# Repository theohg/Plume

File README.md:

<p align="center" width="100%">
  <picture>
    <source media="(prefers-color-scheme: dark)" srcset="./Logos/Plume_logo_light.png">
    <source media="(prefers-color-scheme: light)" srcset="./Logos/Plume_logo_dark.png">
    
  </picture>
</p>

Plume was designed by Théo Heng for the Integrated Actuators Laboratory [(LAI)](https://www.epfl.ch/labs/lai/) in the context of a master semester project. The goal is to develop a microcontroller-based system to independently control a motor array in a reconfigurable insole designed for patients with diabetes, redistributing plantar pressure without the use of position sensors. 

This board is capable to drive and control in position up to 18 Brushed DC motors total and up to 9 simultaneously, without position sensors. This is achieved thanks to the ripple counting technique, integrated in the DRV8214 drivers. 

Plume also integrates multiple other features: 
- Automotive Grade Wireless Charging Qi (WPC v2.0) 
- USB-C charging
- Power Path between USB and Induction
- BLE 5.4
- Adressable RGB LED
- Power LED, Charge LED, Fault LEDs
- Exposed UART and I2C interface
- Tag-Connect 2030 for SWD + SWO
- Battery Protection and Voltage Supervisor
- 6-axis, High Performance, low power IMU
- Motion-Controlled Deep-Sleep mode
- I2C Multiplexer
- Accurate and Low-Power Battery Voltage Sensing

***

***

## SPECIFICATIONS

| Parameter | Plume V1.0 | 
| --- | --- |
| Working Battery Voltage Input | 3.08-4.25 V |
| Typ. Charge Current (USB, wireless)| 455 mA |
| Max. Allowed Charge Current | 2.27 A |
| Max. Continuous Discharge Current | 4.54 A |
| Theoretical Deep Sleep Power Consumption| 15 µA |
| Mass | 23.5g with the frame |
| Communication | UART / Trace Asynchronous (SWD) / I2C |
| MCU | STM32 WB5MMGH6TR |
| Dimensions | 70x40x9mm |
| Cost per PCB    | 39 CHF board + 75 CHF components + 125 CHF assembly ≈ 240 CHF / PCB    |
| Designer   | Théo Heng        |
| Supervisors   | Maël Dagon, Paolo Germano      |
| Development Period       | Feb. - May. 2025 |
| Project    | Smart Footwear for Diabetic Foot Care    |

***

## DIRECTORY STRUCTURE

```
Plume
├── Computations        # Computation sheets and simulations performed
├── Datasheets          # Datasheet of components
├── Images              # Pictures and screenshots used in schematics
├── lib
    |── 3d_models       # Component 3D models
    |── lib_fp          # Footprint libraries
    └── lib_sym         # Symbol libraries
├── Logos               # EPFL and Plume logos
├── Manufacturing
    |── Assembly        # BOM, assembly document
        |── bom.csv     # CSV BOM
        |── bom.html    # HTML BOM
        └── ibom        # HTML interactive BOM
    └── Fabrication     # zipped fabrication documents, and other generated documents by JLCToolkit Pluggin
├── Schematic           # PDF of schematic
├── Software            # Firmware of the Board
    |── PLUME_ESP32     # PlatformIO project for the ESP32-based prototype
    └── PLUME_STM32     # STM32CubeIDE project for the Plume PCB
├── STEP_BLENDER_STL    # Step, .pcb3d and stl files of the PCB and its casing
└── Templates           # Title block templates

```

***

## FIRMWARE

***

## CREDITS

Schematic template & project structure is hugely inspired by the work of Vincent Nguyen on its [Λ M U L E T](https://github.com/EPFLXplore/XRE_LeggedRobot_HW/tree/master/amulet_controller) controler.

***

## PHOTOS

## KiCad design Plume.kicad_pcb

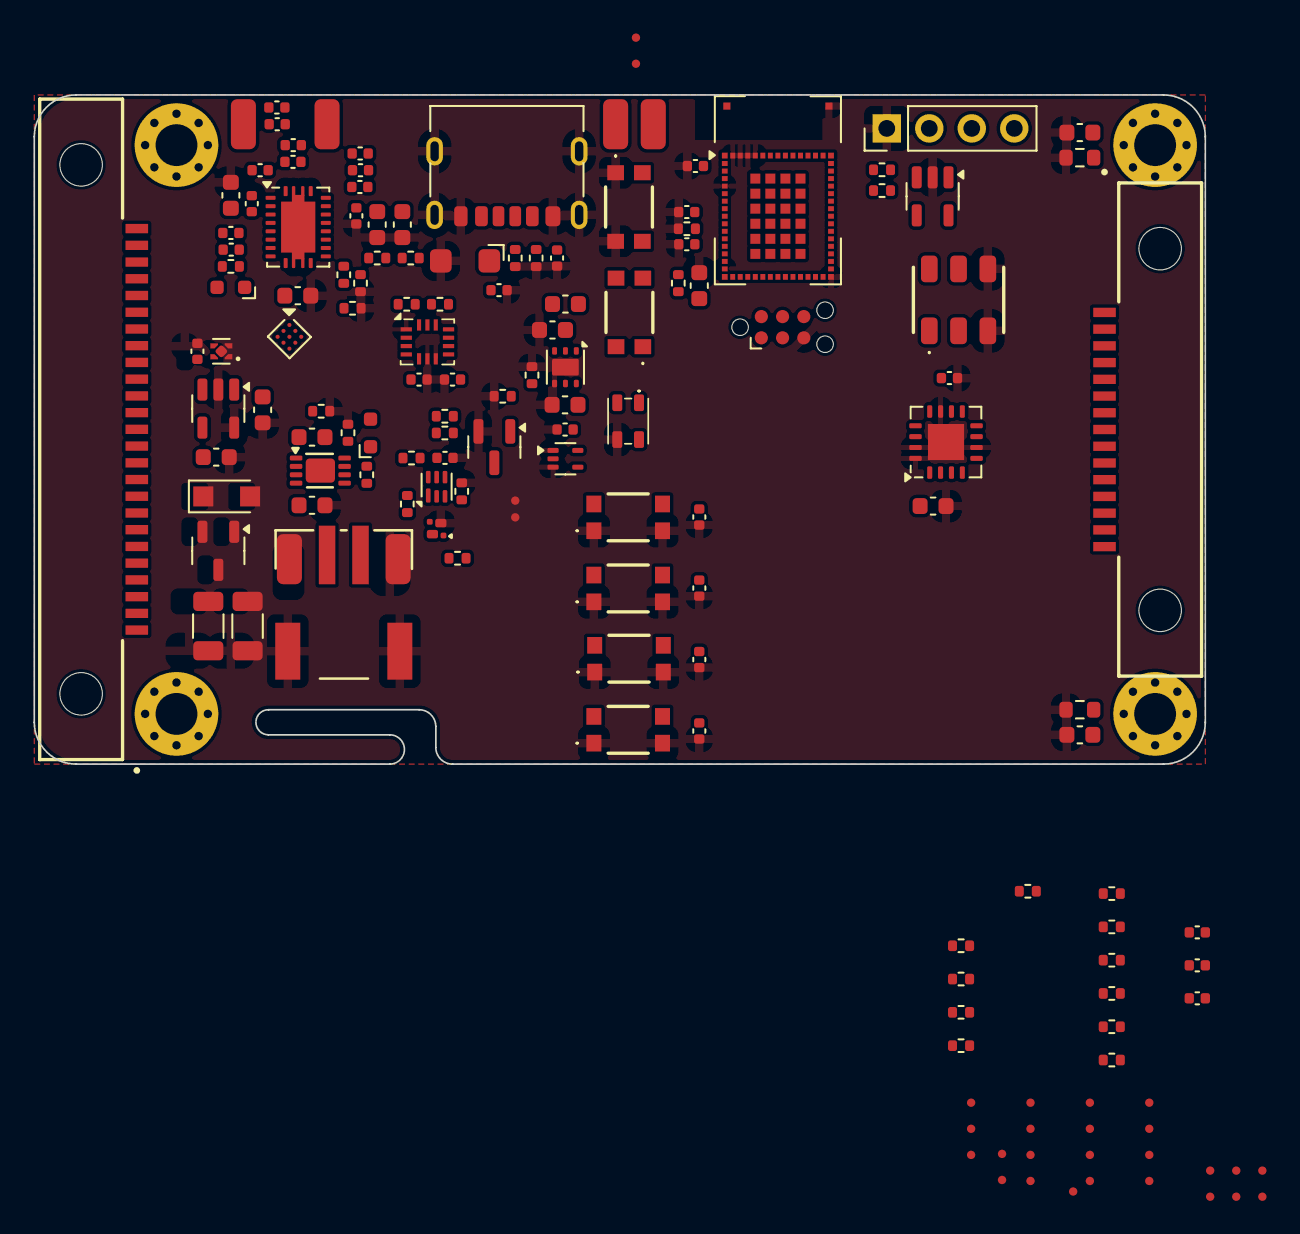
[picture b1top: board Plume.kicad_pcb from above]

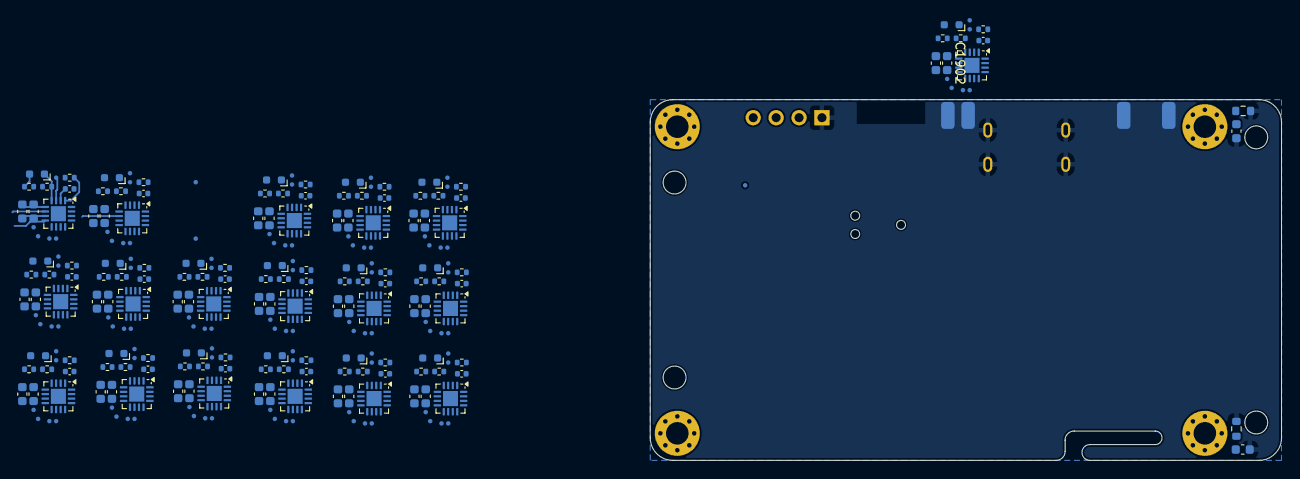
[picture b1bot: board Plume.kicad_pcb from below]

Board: 6 copper layers, 70.0 x 40.0 mm, 418 parts (262 on the bottom side), 203 nets.

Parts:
C401, C402, C404, C405, C406, C407, C502, C503, C601, C604, C605, C616, C701, C802, C1003, C1103, C1203, C1303, C1403, C1503, C1603, C1703, C1803, C1903, C2003, C2103, C2203, C2303, C2403, C2503, C2603, C2703, C2803, C2805, C2806: 100n X7R 16V; C_0402_1005Metric
C403, C501, C504: 4u7 X7R 16V; C_0603_1608Metric
C408, C409, C410: 3p3 C0G 50V; C_0402_1005Metric
C506, C507: 47u X5R 16V; C_1206_3216Metric
C602, C617, C618, C703, C704, C1001, C1101, C1201, C1301, C1401, C1501, C1601, C1701, C1801, C1901, C2001, C2101, C2201, C2301, C2401, C2501, C2601, C2701: 10u X5R 16V; C_0603_1608Metric
C603, C801: 1u X7R 16V; C_0603_1608Metric
C606, C609, C615: 10n C0G 25V; C_0402_1005Metric
C607, C613: 470n X5R 25V; C_0402_1005Metric
C608, C614: 22n X7R 25V; C_0402_1005Metric
C610: 150n X7R 25V; C_0402_1005Metric
C611: 2n2 X7R 25V; C_0402_1005Metric
C612: 390pF X7R 25V; C_0402_1005Metric
C1002, C1102, C1202, C1302, C1402, C1502, C1602, C1702, C1802, C1902, C2002, C2102, C2202, C2302, C2402, C2502, C2602, C2702: 100n X7R 50V; C_0603_1608Metric
C2801: 220n X7R 16V; C_0603_1608Metric
C2802, C2804: 2u2 X7R 16V; C_0603_1608Metric
C2901, C2902, C2903, C2904: 1n X7R 1kV; C_0603_1608Metric
D401: ESDS314; SOT-23-5
D601: TVS SMF5.0A; D_SOD-123FL
D701: Schottky 1N5819W; Nexperia_CFP3_SOD-123W
D2801: IN-PI22TAT5R5G5B; INPI22TAT5R5G5B
H2901, H2902, H2903, H2904: M2.5 (2.7mm); MountingHole_2.5mm_Pad_Via
IC1001, IC1101, IC1201, IC1301, IC1401, IC1501, IC1601, IC1701, IC1801, IC1901, IC2001, IC2101, IC2201, IC2301, IC2401, IC2501, IC2601, IC2701: DRV8214RTER; WQFN-16-1EP_3x3mm_P0.5mm_EP1.68x1.68mm_ThermalVias
IC2801: SN74AHCT1G125DRLR; SOT-553
IC2802: REG71050DRVT; WSON-6-1EP_2x2mm_P0.65mm_EP1x1.6mm
J401: Solder Holes 4x1 2.54mm 22AWG; PinHeader_1x04_P2.54mm_Vertical
J402: Conn_ARM_SWD_TagConnect_TC2030-NL; Tag-Connect_TC2030-IDC-NL_2x03_P1.27mm_Vertical
J403, J404, J405, J406, J407, J408, J602, J603, J604, J605: Solder Wire Pad 1,5x3mm; SolderWirePad_SMD_1,5x3mm
J501: S2B-PH-SM4-TB; CONN_S2B-PH-SM4-TB_JST
J601: USB_C_Receptacle_PowerOnly_6P; USB4125-GF-A
J901: SEI-125-02-GF-S-M-AT; SAMTEC_SEI-125-02-GF-S-M-AT
J902: SEI-115-02-GF-S-M-AT; SAMTEC_SEI-115-02-GF-S-M-AT
LED501, LED502: GREEN; KingBright_LED_0603
LED1001, LED1101, LED1201, LED1301, LED1401, LED1501, LED1601, LED1701, LED1801, LED1901, LED2001, LED2101, LED2201, LED2301, LED2401, LED2501, LED2601, LED2701: BLUE; KingBright_LED_0603
Q501: NMOS IRLML6344TRPBF SOT-23; SOT-23
Q502: CSD85302L
Q601: CSD75207W15; Texas_DSBGA-9_1.62x1.58mm_Layout3x3_P0.5mm
Q701: PMOS SI2365EDS-T1-GE3; SOT-23-3
R401, R501, R505, R510, R1002, R1102, R1202, R1302, R1402, R1502, R1602, R1702, R1802, R1902, R2002, R2102, R2202, R2302, R2402, R2502, R2602, R2702: 330R 1%; R_0402_1005Metric
R403, R404: 22R 1%; R_0402_1005Metric
R502, R802, R803, R804, R805, R806, R807, R808, R809, R810, R811, R812, R813: 3k 1%; R_0402_1005Metric
R503, R605, R606, R608, R609: 10k 1%; R_0402_1005Metric
R504, R508: 2k2 1%; R_0402_1005Metric
R506, R507: 4M99 1%; R_0402_1005Metric
R509, R701, R801, R1003, R1103, R1203, R1303, R1403, R1503, R1603, R1703, R1803, R1903, R2003, R2103, R2203, R2303, R2403, R2503, R2603, R2703, R2801: 100k 1%; R_0402_1005Metric
R602, R603: 5k1 1%; R_0402_1005Metric
R604, R607: 196R 1%; R_0402_1005Metric
R1001, R1101, R1201, R1301, R1401, R1501, R1601, R1701, R1801, R1901, R2001, R2101, R2201, R2301, R2401, R2501, R2601, R2701: 680R 1%; R_0402_1005Metric
R2901, R2902, R2903, R2904: 0R 1%; R_0603_1608Metric
SW401, SW402, SW404, SW405, SW406, SW407: KMR232NG ULC; KMR232NGULCLFS
SW403: CAS-D20A1; CAS-D2xx
TP401: BUTTON1; TestPoint_Pad_D0.5mm_Back
TP402: BUTTON2; TestPoint_Pad_D0.5mm_Back
TP403: BUTTON3; TestPoint_Pad_D0.5mm_Back
TP404: BUTTON4; TestPoint_Pad_D0.5mm_Back
TP405: SWITCH1; TestPoint_Pad_D0.5mm_Back
TP406: SWITCH2; TestPoint_Pad_D0.5mm_Back
TP501: COUT; TestPoint_Pad_D0.5mm_Back
TP502: DOUT; TestPoint_Pad_D0.5mm_Back
TP503: CHARGE_STATUS; TestPoint_Pad_D0.5mm_Back
TP504: BAT_SENSE_EN; TestPoint_Pad_D0.5mm_Back
TP505: BAT_SENSE; TestPoint_Pad_D0.5mm_Back
TP506: -VBAT; TestPoint_Pad_D0.5mm_Back
TP507: VBAT; TestPoint_Pad_D0.5mm_Back
TP601: +VBUS; TestPoint_Pad_D0.5mm_Back
TP602: +VCHARGE; TestPoint_Pad_D0.5mm_Back
TP603: ~{AD_EN}; TestPoint_Pad_D0.5mm_Back
TP604: ~{CHG}; TestPoint_Pad_D0.5mm_Back
TP701: 3V3_EN; TestPoint_Pad_D0.5mm_Back
TP702, TP802: +3V3; TestPoint_Pad_D0.5mm_Back
TP703: +VDD; TestPoint_Pad_D0.5mm_Back
TP801: MUX_RESET; TestPoint_Pad_D0.5mm_Back
TP901: nSLEEP_FRONT; TestPoint_Pad_D0.5mm_Back
TP902: nSLEEP_REAR; TestPoint_Pad_D0.5mm_Back
TP1001, TP1101, TP1201, TP1301, TP1401, TP1501, TP1601, TP1701, TP1801, TP1901, TP2001, TP2101, TP2201, TP2301, TP2401, TP2501, TP2601, TP2701: nFAULT; TestPoint_Pad_D0.5mm_Back
TP1002, TP1102, TP1202, TP1302, TP1402, TP1502, TP1602, TP1702, TP1802, TP1902, TP2002, TP2102, TP2202, TP2302, TP2402, TP2502, TP2602, TP2702: RC_OUT; TestPoint_Pad_D0.5mm_Back
TP1003, TP1103, TP1203, TP1303, TP1403, TP1503, TP1603, TP1703, TP1803, TP1903, TP2003, TP2103, TP2203, TP2303, TP2403, TP2503, TP2603, TP2703: OUT1; TestPoint_Pad_D0.5mm_Back
TP1004, TP1104, TP1204, TP1304, TP1404, TP1504, TP1604, TP1704, TP1804, TP1904, TP2004, TP2104, TP2204, TP2304, TP2404, TP2504, TP2604, TP2704: OUT2; TestPoint_Pad_D0.5mm_Back
TP1005, TP1105, TP1205, TP1305, TP1405, TP1505, TP1605, TP1705, TP1805, TP1905, TP2005, TP2105, TP2205, TP2305, TP2405, TP2505, TP2605, TP2705: A0; TestPoint_Pad_D0.5mm_Back
TP1006, TP1106, TP1206, TP1306, TP1406, TP1506, TP1606, TP1706, TP1806, TP1906, TP2006, TP2106, TP2206, TP2306, TP2406, TP2506, TP2606, TP2706: A1; TestPoint_Pad_D0.5mm_Back
TP2801: 5V_ENABLE; TestPoint_Pad_D0.5mm_Back
TP2802: DIN_3V3; TestPoint_Pad_D0.5mm_Back
TP2803, TP2807: INT1; TestPoint_Pad_D0.5mm_Back
TP2804, TP2808: INT2; TestPoint_Pad_D0.5mm_Back
U401: STM32WB5MMGH6TR; ST-SiP-LGA-86-11x7.3mm
U501: BQ29737DSER; WSON-6_1.5x1.5mm_P0.5mm
U502: MCP73831T-2ACI/MC; DFN_2x3mm
U601: BQ51013CQWRHLRQ1; Texas_VQFN-RHL-20
U701: TPS3839G33DQNR; Texas_X2SON-4_1x1mm_P0.65mm
U702: TPS7A0233DBVR; SOT-23-5
U801: PCA9546ARGVR; Texas_RSA_VQFN-16-1EP_4x4mm_P0.65mm_EP2.16x2.16mm
U3202: BMI270; Bosch_LGA-14_3x2.5mm_P0.5mm

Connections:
+3V3: C403.1, C703.1, C801.1, C802.1, C2804.1, C2805.1, C2806.1, D401.5 (I/O4), IC1201.10 (A0), IC1501.10 (A0), IC1601.9 (A1), IC1701.9 (A1), IC1801.9 (A1), IC1801.10 (A0), IC2101.10 (A0), IC2401.10 (A0), IC2501.9 (A1), IC2601.9 (A1), IC2701.9 (A1), IC2701.10 (A0), IC2802.2 (V_IN), J401.4, J402.1 (VCC), R801.1, R802.1, R803.1, R804.1, R805.1, R806.1, R807.1, R808.1, R809.1, R810.1, R811.1, R812.1, R813.1, R1002.1, R1003.1, R1102.1, R1103.1, R1202.1, R1203.1, R1302.1, R1303.1, R1402.1, R1403.1, R1502.1, R1503.1, R1602.1, R1603.1, R1702.1, R1703.1, R1802.1, R1803.1, R1902.1, R1903.1, R2002.1, R2003.1, R2102.1, R2103.1, R2202.1, R2203.1, R2302.1, R2303.1, R2402.1, R2403.1, R2502.1, R2503.1, R2602.1, R2603.1, R2702.1, R2703.1, SW401.2, SW401.3, SW403.1, SW403.4, TP702.1, TP802.1, TP1205.1, TP1505.1, TP1606.1, TP1706.1, TP1805.1, TP1806.1, TP2105.1, TP2405.1, TP2506.1, TP2606.1, TP2705.1, TP2706.1, U401.4 (VREF), U401.6 (VDDA), U401.15 (VBAT), U401.17 (VDDSMPS), U401.32 (VDDUSB), U702.1 (OUT), U801.14 (VCC), U3202.5 (VDDIO), U3202.8 (VDD), U3202.12 (CSB)
+VBUS: C603.1, C604.1, C605.1, D601.1 (K), J601.A9 (VBUS), J601.B9 (VBUS), Q601.2 (D1), Q601.3 (D1), Q601.6 (D1), TP601.1, U601.9 (AD)
/Project Architecture/Logic - I2C Mux/I2C1_SCL: R803.2, U401.14 (PB8), U801.12 (SCL)
/Project Architecture/Logic - I2C Mux/I2C1_SDA: R802.2, U401.11 (PB9), U801.13 (SDA)
/Project Architecture/Logic - I2C Mux/MUX_RESET: R801.2, TP801.1, U801.1 (RESET)
/Project Architecture/Logic - I2C Mux/SC0: R804.2, U801.3 (SC0)
/Project Architecture/Logic - I2C Mux/SC1: R810.2, U801.5 (SC1)
/Project Architecture/Logic - I2C Mux/SC2: R809.2, U801.7 (SD2)
/Project Architecture/Logic - I2C Mux/SC3: R807.2, U801.9 (SD3)
/Project Architecture/Logic - I2C Mux/SD0: R805.2, U801.2 (SD0)
/Project Architecture/Logic - I2C Mux/SD1: R811.2, U801.4 (SD1)
/Project Architecture/Logic - I2C Mux/SD2: R808.2, U801.8 (SC2)
/Project Architecture/Logic - I2C Mux/SD3: R806.2, U801.10 (SC3)
/Project Architecture/MCU - Unit/5V_ENABLE: IC2802.5 (ENABLE), R2801.1, TP2801.1, U401.8 (PC2)
/Project Architecture/MCU - Unit/BAT_SENSE: C502.2, R502.2, R503.1, TP505.1, U401.2 (PA1)
/Project Architecture/MCU - Unit/BAT_SENSE_EN: Q501.1 (G), R509.1, TP504.1, U401.3 (PA0)
/Project Architecture/MCU - Unit/BOOT0: C401.1, R401.2, R609.2, U401.13 (PH3-BOOT0)
/Project Architecture/MCU - Unit/BOOT0_B: R401.1, SW401.1, SW401.4
/Project Architecture/MCU - Unit/BUTTON1: C404.1, SW404.2, SW404.3, TP401.1, U401.18 (PB7)
/Project Architecture/MCU - Unit/BUTTON2: C405.1, SW405.2, SW405.3, TP402.1, U401.19 (PB5)
/Project Architecture/MCU - Unit/BUTTON3: C406.1, SW406.2, SW406.3, TP403.1, U401.20 (PB4)
/Project Architecture/MCU - Unit/BUTTON4: C407.1, SW407.2, SW407.3, TP404.1, U401.22 (PC10)
/Project Architecture/MCU - Unit/CHARGE_STATUS: R505.2, TP503.1, U502.5 (STAT)
/Project Architecture/MCU - Unit/DIN_3V3: IC2801.2 (A), TP2802.1, U401.7 (PC3)
/Project Architecture/MCU - Unit/EN1: U401.56 (PA3), U601.10 (EN1)
/Project Architecture/MCU - Unit/EN2: U401.1 (PA2), U601.11 (EN2)
/Project Architecture/MCU - Unit/I2C3_SCL: J403.1, J408.1, R813.2, U401.12 (PC0), U3202.13 (SCx)
/Project Architecture/MCU - Unit/I2C3_SDA: J404.1, J407.1, R812.2, U401.9 (PC1), U3202.14 (SDx)
/Project Architecture/MCU - Unit/SWCLK: J402.4 (SWCLK), U401.26 (PA14)
/Project Architecture/MCU - Unit/SWDIO: J402.2 (SWDIO), U401.25 (PA13)
/Project Architecture/MCU - Unit/SWITCH1: SW403.5, TP405.1
/Project Architecture/MCU - Unit/SWITCH2: SW403.2, TP406.1
/Project Architecture/MCU - Unit/SWO: J402.6 (SWO), U401.21 (PB3)
/Project Architecture/MCU - Unit/USART1_RX: R404.1, U401.28 (PA10)
/Project Architecture/MCU - Unit/USART1_RX_C: D401.1 (I/O1), D401.3 (I/O2), J401.2, J401.3, R403.2, R404.2
/Project Architecture/MCU - Unit/USART1_TX: R403.1, U401.51 (PA9)
/Project Architecture/MCU - Unit/nFault0: IC1001.4 (nFAULT), LED1001.1 (K), R1003.2, TP1001.1, U401.50 (PA8)
/Project Architecture/MCU - Unit/nFault1: IC1101.4 (nFAULT), LED1101.1 (K), R1103.2, TP1101.1, U401.49 (PC4)
/Project Architecture/MCU - Unit/nFault2: IC1201.4 (nFAULT), LED1201.1 (K), R1203.2, TP1201.1, U401.48 (PB2)
/Project Architecture/MCU - Unit/nFault3: C408.1, IC1301.4 (nFAULT), LED1301.1 (K), R1303.2, TP1301.1, U401.47 (PB10)
/Project Architecture/MCU - Unit/nFault4: C409.1, IC1401.4 (nFAULT), LED1401.1 (K), R1403.2, TP1401.1, U401.46 (PB11)
/Project Architecture/MCU - Unit/nFault5: C410.1, IC1501.4 (nFAULT), LED1501.1 (K), R1503.2, TP1501.1, U401.45 (PC5)
/Project Architecture/MCU - Unit/nFault6: IC1601.4 (nFAULT), LED1601.1 (K), R1603.2, TP1601.1, U401.44 (PB0)
/Project Architecture/MCU - Unit/nFault7: IC1701.4 (nFAULT), LED1701.1 (K), R1703.2, TP1701.1, U401.43 (PB1)
/Project Architecture/MCU - Unit/nFault8: IC1801.4 (nFAULT), LED1801.1 (K), R1803.2, TP1801.1, U401.42 (PE4)
/Project Architecture/MCU - Unit/nFault9: IC1901.4 (nFAULT), LED1901.1 (K), R1903.2, TP1901.1, U401.41 (PB12)
/Project Architecture/MCU - Unit/nFault10: IC2001.4 (nFAULT), LED2001.1 (K), R2003.2, TP2001.1, U401.40 (PC13)
/Project Architecture/MCU - Unit/nFault11: IC2101.4 (nFAULT), LED2101.1 (K), R2103.2, TP2101.1, U401.39 (PB6)
/Project Architecture/MCU - Unit/nFault12: IC2201.4 (nFAULT), LED2201.1 (K), R2203.2, TP2201.1, U401.38 (PB15)
/Project Architecture/MCU - Unit/nFault13: IC2301.4 (nFAULT), LED2301.1 (K), R2303.2, TP2301.1, U401.37 (PB14)
/Project Architecture/MCU - Unit/nFault14: IC2401.4 (nFAULT), LED2401.1 (K), R2403.2, TP2401.1, U401.36 (PC6)
/Project Architecture/MCU - Unit/nFault15: IC2501.4 (nFAULT), LED2501.1 (K), R2503.2, TP2501.1, U401.35 (PB13)
/Project Architecture/MCU - Unit/nFault16: IC2601.4 (nFAULT), LED2601.1 (K), R2603.2, TP2601.1, U401.34 (PD1)
/Project Architecture/MCU - Unit/nFault17: IC2701.4 (nFAULT), LED2701.1 (K), R2703.2, TP2701.1, U401.33 (PD0)
/Project Architecture/MCU - Unit/nSLEEP_FRONT: IC1001.11 (nSLEEP), IC1101.11 (nSLEEP), IC1201.11 (nSLEEP), IC1301.11 (nSLEEP), IC1401.11 (nSLEEP), IC1501.11 (nSLEEP), IC1601.11 (nSLEEP), IC1701.11 (nSLEEP), IC1801.11 (nSLEEP), IC1901.11 (nSLEEP), IC2001.11 (nSLEEP), TP901.1
/Project Architecture/MCU - Unit/nSLEEP_REAR: IC2101.11 (nSLEEP), IC2201.11 (nSLEEP), IC2301.11 (nSLEEP), IC2401.11 (nSLEEP), IC2501.11 (nSLEEP), IC2601.11 (nSLEEP), IC2701.11 (nSLEEP), TP902.1
/Project Architecture/MCU - Unit/~RESET: C402.1, J402.3 (~RESET), SW402.2, SW402.3, U401.10 (NRST)
/Project Architecture/Misc - Mounting Holes & Fiducials/HOLE1: C2901.1, H2901.1, R2901.1
/Project Architecture/Misc - Mounting Holes & Fiducials/HOLE2: C2902.1, H2902.1, R2902.1
/Project Architecture/Misc - Mounting Holes & Fiducials/HOLE3: C2903.1, H2903.1, R2903.1
/Project Architecture/Misc - Mounting Holes & Fiducials/HOLE4: C2904.1, H2904.1, R2904.1
/Project Architecture/Motor Control - Drivers/Motor Control - Driver 0/FAULT_LED: LED1001.2 (A), R1002.2
/Project Architecture/Motor Control - Drivers/Motor Control - Driver 0/RC_OUT: IC1001.3 (RC_OUT), TP1002.1
/Project Architecture/Motor Control - Drivers/Motor Control - Driver 1/A0: IC1101.10 (A0), TP1105.1
/Project Architecture/Motor Control - Drivers/Motor Control - Driver 1/FAULT_LED: LED1101.2 (A), R1102.2
/Project Architecture/Motor Control - Drivers/Motor Control - Driver 1/RC_OUT: IC1101.3 (RC_OUT), TP1102.1
/Project Architecture/Motor Control - Drivers/Motor Control - Driver 2/FAULT_LED: LED1201.2 (A), R1202.2
/Project Architecture/Motor Control - Drivers/Motor Control - Driver 2/RC_OUT: IC1201.3 (RC_OUT), TP1202.1
/Project Architecture/Motor Control - Drivers/Motor Control - Driver 3/A1: IC1301.9 (A1), TP1306.1
/Project Architecture/Motor Control - Drivers/Motor Control - Driver 3/FAULT_LED: LED1301.2 (A), R1302.2
/Project Architecture/Motor Control - Drivers/Motor Control - Driver 3/RC_OUT: IC1301.3 (RC_OUT), TP1302.1
/Project Architecture/Motor Control - Drivers/Motor Control - Driver 4/A0: IC1401.10 (A0), TP1405.1
/Project Architecture/Motor Control - Drivers/Motor Control - Driver 4/A1: IC1401.9 (A1), TP1406.1
/Project Architecture/Motor Control - Drivers/Motor Control - Driver 4/FAULT_LED: LED1401.2 (A), R1402.2
/Project Architecture/Motor Control - Drivers/Motor Control - Driver 4/RC_OUT: IC1401.3 (RC_OUT), TP1402.1
/Project Architecture/Motor Control - Drivers/Motor Control - Driver 5/A1: IC1501.9 (A1), TP1506.1
/Project Architecture/Motor Control - Drivers/Motor Control - Driver 5/FAULT_LED: LED1501.2 (A), R1502.2
/Project Architecture/Motor Control - Drivers/Motor Control - Driver 5/RC_OUT: IC1501.3 (RC_OUT), TP1502.1
/Project Architecture/Motor Control - Drivers/Motor Control - Driver 6/FAULT_LED: LED1601.2 (A), R1602.2
/Project Architecture/Motor Control - Drivers/Motor Control - Driver 6/RC_OUT: IC1601.3 (RC_OUT), TP1602.1
/Project Architecture/Motor Control - Drivers/Motor Control - Driver 7/A0: IC1701.10 (A0), TP1705.1
/Project Architecture/Motor Control - Drivers/Motor Control - Driver 7/FAULT_LED: LED1701.2 (A), R1702.2
/Project Architecture/Motor Control - Drivers/Motor Control - Driver 7/RC_OUT: IC1701.3 (RC_OUT), TP1702.1
/Project Architecture/Motor Control - Drivers/Motor Control - Driver 8/FAULT_LED: LED1801.2 (A), R1802.2
/Project Architecture/Motor Control - Drivers/Motor Control - Driver 8/RC_OUT: IC1801.3 (RC_OUT), TP1802.1
/Project Architecture/Motor Control - Drivers/Motor Control - Driver 9/FAULT_LED: LED1901.2 (A), R1902.2
/Project Architecture/Motor Control - Drivers/Motor Control - Driver 9/RC_OUT: IC1901.3 (RC_OUT), TP1902.1
/Project Architecture/Motor Control - Drivers/Motor Control - Driver 10/A0: IC2001.10 (A0), TP2005.1
/Project Architecture/Motor Control - Drivers/Motor Control - Driver 10/FAULT_L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: LED2001.2 (A), R2002.2
/Project Architecture/Motor Control - Drivers/Motor Control - Driver 10/RC_OUT: IC2001.3 (RC_OUT), TP2002.1
/Project Architecture/Motor Control - Drivers/Motor Control - Driver 11/FAULT_L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: LED2101.2 (A), R2102.2
/Project Architecture/Motor Control - Drivers/Motor Control - Driver 11/RC_OUT: IC2101.3 (RC_OUT), TP2102.1
/Project Architecture/Motor Control - Drivers/Motor Control - Driver 12/A1: IC2201.9 (A1), TP2206.1
/Project Architecture/Motor Control - Drivers/Motor Control - Driver 12/FAULT_L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: LED2201.2 (A), R2202.2
/Project Architecture/Motor Control - Drivers/Motor Control - Driver 12/RC_OUT: IC2201.3 (RC_OUT), TP2202.1
/Project Architecture/Motor Control - Drivers/Motor Control - Driver 13/A0: IC2301.10 (A0), TP2305.1
/Project Architecture/Motor Control - Drivers/Motor Control - Driver 13/A1: IC2301.9 (A1), TP2306.1
/Project Architecture/Motor Control - Drivers/Motor Control - Driver 13/FAULT_L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: LED2301.2 (A), R2302.2
/Project Architecture/Motor Control - Drivers/Motor Control - Driver 13/RC_OUT: IC2301.3 (RC_OUT), TP2302.1
/Project Architecture/Motor Control - Drivers/Motor Control - Driver 14/A1: IC2401.9 (A1), TP2406.1
/Project Architecture/Motor Control - Drivers/Motor Control - Driver 14/FAULT_L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: LED2401.2 (A), R2402.2
/Project Architecture/Motor Control - Drivers/Motor Control - Driver 14/RC_OUT: IC2401.3 (RC_OUT), TP2402.1
/Project Architecture/Motor Control - Drivers/Motor Control - Driver 15/FAULT_L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: LED2501.2 (A), R2502.2
/Project Architecture/Motor Control - Drivers/Motor Control - Driver 15/RC_OUT: IC2501.3 (RC_OUT), TP2502.1
/Project Architecture/Motor Control - Drivers/Motor Control - Driver 16/A0: IC2601.10 (A0), TP2605.1
/Project Architecture/Motor Control - Drivers/Motor Control - Driver 16/FAULT_L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: LED2601.2 (A), R2602.2
/Project Architecture/Motor Control - Drivers/Motor Control - Driver 16/RC_OUT: IC2601.3 (RC_OUT), TP2602.1
/Project Architecture/Motor Control - Drivers/Motor Control - Driver 17/FAULT_L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: LED2701.2 (A), R2702.2
/Project Architecture/Motor Control - Drivers/Motor Control - Driver 17/RC_OUT: IC2701.3 (RC_OUT), TP2702.1
/Project Architecture/Motor Control - Drivers/OUT1_0: IC1001.6 (OUT1), J901.2, TP1003.1
/Project Architecture/Motor Control - Drivers/OUT1_1: IC1101.6 (OUT1), J901.4, TP1103.1
/Project Architecture/Motor Control - Drivers/OUT1_2: IC1201.6 (OUT1), J901.6, TP1203.1
/Project Architecture/Motor Control - Drivers/OUT1_3: IC1301.6 (OUT1), J901.8, TP1303.1
/Project Architecture/Motor Control - Drivers/OUT1_4: IC1401.6 (OUT1), J901.10, TP1403.1
/Project Architecture/Motor Control - Drivers/OUT1_5: IC1501.6 (OUT1), J901.12, TP1503.1
/Project Architecture/Motor Control - Drivers/OUT1_6: IC1601.6 (OUT1), J901.15, TP1603.1
/Project Architecture/Motor Control - Drivers/OUT1_7: IC1701.6 (OUT1), J901.17, TP1703.1
/Project Architecture/Motor Control - Drivers/OUT1_8: IC1801.6 (OUT1), J901.19, TP1803.1
/Project Architecture/Motor Control - Drivers/OUT1_9: IC1901.6 (OUT1), J901.21, TP1903.1
/Project Architecture/Motor Control - Drivers/OUT1_10: IC2001.6 (OUT1), J901.23, TP2003.1
/Project Architecture/Motor Control - Drivers/OUT1_11: IC2101.6 (OUT1), J902.1, TP2103.1
/Project Architecture/Motor Control - Drivers/OUT1_12: IC2201.6 (OUT1), J902.3, TP2203.1
/Project Architecture/Motor Control - Drivers/OUT1_13: IC2301.6 (OUT1), J902.5, TP2303.1
/Project Architecture/Motor Control - Drivers/OUT1_14: IC2401.6 (OUT1), J902.8, TP2403.1
/Project Architecture/Motor Control - Drivers/OUT1_15: IC2501.6 (OUT1), J902.10, TP2503.1
/Project Architecture/Motor Control - Drivers/OUT1_16: IC2601.6 (OUT1), J902.12, TP2603.1
/Project Architecture/Motor Control - Drivers/OUT1_17: IC2701.6 (OUT1), J902.14, TP2703.1
/Project Architecture/Motor Control - Drivers/OUT2_0: IC1001.8 (OUT2), J901.3, TP1004.1
/Project Architecture/Motor Control - Drivers/OUT2_1: IC1101.8 (OUT2), J901.5, TP1104.1
/Project Architecture/Motor Control - Drivers/OUT2_2: IC1201.8 (OUT2), J901.7, TP1204.1
/Project Architecture/Motor Control - Drivers/OUT2_3: IC1301.8 (OUT2), J901.9, TP1304.1
/Project Architecture/Motor Control - Drivers/OUT2_4: IC1401.8 (OUT2), J901.11, TP1404.1
/Project Architecture/Motor Control - Drivers/OUT2_5: IC1501.8 (OUT2), J901.14, TP1504.1
/Project Architecture/Motor Control - Drivers/OUT2_6: IC1601.8 (OUT2), J901.16, TP1604.1
/Project Architecture/Motor Control - Drivers/OUT2_7: IC1701.8 (OUT2), J901.18, TP1704.1
/Project Architecture/Motor Control - Drivers/OUT2_8: IC1801.8 (OUT2), J901.20, TP1804.1
/Project Architecture/Motor Control - Drivers/OUT2_9: IC1901.8 (OUT2), J901.22, TP1904.1
/Project Architecture/Motor Control - Drivers/OUT2_10: IC2001.8 (OUT2), J901.24, TP2004.1
/Project Architecture/Motor Control - Drivers/OUT2_11: IC2101.8 (OUT2), J902.2, TP2104.1
/Project Architecture/Motor Control - Drivers/OUT2_12: IC2201.8 (OUT2), J902.4, TP2204.1
/Project Architecture/Motor Control - Drivers/OUT2_13: IC2301.8 (OUT2), J902.6, TP2304.1
/Project Architecture/Motor Control - Drivers/OUT2_14: IC2401.8 (OUT2), J902.9, TP2404.1
/Project Architecture/Motor Control - Drivers/OUT2_15: IC2501.8 (OUT2), J902.11, TP2504.1
/Project Architecture/Motor Control - Drivers/OUT2_16: IC2601.8 (OUT2), J902.13, TP2604.1
/Project Architecture/Motor Control - Drivers/OUT2_17: IC2701.8 (OUT2), J902.15, TP2704.1
/Project Architecture/Motor Control - Drivers/SC0: IC1001.15 (SCL), IC1101.15 (SCL), IC1201.15 (SCL), IC1301.15 (SCL), IC1401.15 (SCL), IC1501.15 (SCL), IC1601.15 (SCL), IC1701.15 (SCL), IC1801.15 (SCL)
/Project Architecture/Motor Control - Drivers/SC1: IC1901.15 (SCL), IC2001.15 (SCL), IC2101.15 (SCL), IC2201.15 (SCL), IC2301.15 (SCL), IC2401.15 (SCL), IC2501.15 (SCL), IC2601.15 (SCL), IC2701.15 (SCL)
/Project Architecture/Motor Control - Drivers/SD0: IC1001.14 (SDA), IC1101.14 (SDA), IC1201.14 (SDA), IC1301.14 (SDA), IC1401.14 (SDA), IC1501.14 (SDA), IC1601.14 (SDA), IC1701.14 (SDA), IC1801.14 (SDA)
/Project Architecture/Motor Control - Drivers/SD1: IC1901.14 (SDA), IC2001.14 (SDA), IC2101.14 (SDA), IC2201.14 (SDA), IC2301.14 (SDA), IC2401.14 (SDA), IC2501.14 (SDA), IC2601.14 (SDA), IC2701.14 (SDA)
/Project Architecture/Power - Battery Management/+VBAT: C501.2, C506.1, C507.2, C1001.1, C1002.1, C1003.1, C1101.1, C1102.1, C1103.1, C1201.1, C1202.1, C1203.1, C1301.1, C1302.1, C1303.1, C1401.1, C1402.1, C1403.1, C1501.1, C1502.1, C1503.1, C1601.1, C1602.1, C1603.1, C1701.1, C1702.1, C1703.1, C1801.1, C1802.1, C1803.1, C1901.1, C1902.1, C1903.1, C2001.1, C2002.1, C2003.1, C2101.1, C2102.1, C2103.1, C2201.1, C2202.1, C2203.1, C2301.1, C2302.1, C2303.1, C2401.1, C2402.1, C2403.1, C2501.1, C2502.1, C2503.1, C2601.1, C2602.1, C2603.1, C2701.1, C2702.1, C2703.1, IC1001.2 (VCC), IC1001.5 (VM), IC1101.2 (VCC), IC1101.5 (VM), IC1201.2 (VCC), IC1201.5 (VM), IC1301.2 (VCC), IC1301.5 (VM), IC1401.2 (VCC), IC1401.5 (VM), IC1501.2 (VCC), IC1501.5 (VM), IC1601.2 (VCC), IC1601.5 (VM), IC1701.2 (VCC), IC1701.5 (VM), IC1801.2 (VCC), IC1801.5 (VM), IC1901.2 (VCC), IC1901.5 (VM), IC2001.2 (VCC), IC2001.5 (VM), IC2101.2 (VCC), IC2101.5 (VM), IC2201.2 (VCC), IC2201.5 (VM), IC2301.2 (VCC), IC2301.5 (VM), IC2401.2 (VCC), IC2401.5 (VM), IC2501.2 (VCC), IC2501.5 (VM), IC2601.2 (VCC), IC2601.5 (VM), IC2701.2 (VCC), IC2701.5 (VM), J405.1, J501.1, Q701.3 (D), R501.1, R502.1, TP507.1, U502.3 (V_{BAT}), U502.4 (V_{BAT})
/Project Architecture/Power - Battery Management/-VBAT: J501.2, Q502.S1, R504.2, R506.2, TP506.1
/Project Architecture/Power - Battery Management/BAT: C503.2, R501.2, U501.5 (BAT)
/Project Architecture/Power - Battery Management/CHARGE_LED: LED501.1 (K), R505.1
/Project Architecture/Power - Battery Management/COUT: Q502.G1, R506.1, TP501.1, U501.2 (Cout)
/Project Architecture/Power - Battery Management/DOUT: Q502.G2, R507.2, TP502.1, U501.3 (Dout)
/Project Architecture/Power - Battery Management/PROG: R508.1, U502.8 (PROG)
/Project Architecture/Power - Battery Management/V-: R504.1, U501.6 (V-)
/Project Architecture/Power - Path & Generation/3V3_EN: TP701.1, U701.1 (~RESET), U702.3 (EN)
/Project Architecture/Power - Path & Generation/+VDD: C701.1, C704.1, D701.1 (K), Q701.2 (S), TP703.1, U701.4 (VDD), U702.4 (IN)
/Project Architecture/Power - Wireless Receiver & USB/+VCHARGE: C504.2, C601.1, C602.1, D701.2 (A), LED501.2 (A), LED502.2 (A), Q601.5 (D2), Q601.8 (D2), Q601.9 (D2), Q701.1 (G), R701.1, TP602.1, U502.1 (V_{DD}), U502.2 (V_{DD}), U601.4 (OUT)
/Project Architecture/Power - Wireless Receiver & USB/AC1: C606.2, C607.2, C608.2, C609.2, C610.2, C611.1, C612.1, U601.2 (AC1)
/Project Architecture/Power - Wireless Receiver & USB/AC2: C611.2, C612.2, C613.1, C614.1, C615.1, J603.1, J604.1, U601.19 (AC2)
/Project Architecture/Power - Wireless Receiver & USB/BOOT1: C609.1, U601.3 (BOOT1)
/Project Architecture/Power - Wireless Receiver & USB/BOOT2: C615.2, U601.17 (BOOT2)
/Project Architecture/Power - Wireless Receiver & USB/CC1: J601.A5 (CC1), R602.2
/Project Architecture/Power - Wireless Receiver & USB/CC2: J601.B5 (CC2), R603.2
/Project Architecture/Power - Wireless Receiver & USB/CLAMP1: C607.1, U601.5 (CLAMP1)
/Project Architecture/Power - Wireless Receiver & USB/CLAMP2: C613.2, U601.16 (CLAMP2)
/Project Architecture/Power - Wireless Receiver & USB/COIL1: C606.1, C610.1, J602.1, J605.1
/Project Architecture/Power - Wireless Receiver & USB/COMM1: C608.1, U601.6 (COMM1)
/Project Architecture/Power - Wireless Receiver & USB/COMM2: C614.2, U601.15 (COMM2)
/Project Architecture/Power - Wireless Receiver & USB/FOD: R604.2, R606.2, R607.1, U601.14 (FOD)
/Project Architecture/Power - Wireless Receiver & USB/ILIM: R604.1, U601.12 (ILIM)
/Project Architecture/Power - Wireless Receiver & USB/RECT: C616.1, C617.1, C618.1, R605.1, U601.18 (RECT)
/Project Architecture/Power - Wireless Receiver & USB/TS/CTRL: R608.2, U601.13 (TS/CTRL)
/Project Architecture/Power - Wireless Receiver & USB/~AD_EN: Q601.1 (G1), Q601.7 (G2), TP603.1, U601.8 (~AD-EN)
/Project Architecture/Power - Wireless Receiver & USB/~CHG: R510.2, TP604.1, U601.7 (~CHG)
/Project Architecture/User - RGB LED Indicator/+5V: C2802.1, C2803.1, D2801.1 (VDD), IC2801.5 (VCC), IC2802.6 (VOUT), TP2804.1
/Project Architecture/User - RGB LED Indicator/CPUMP+: C2801.1, IC2802.1 (CPUMP+)
/Project Architecture/User - RGB LED Indicator/CPUMP-: C2801.2, IC2802.3 (C_PUMP-)
/Project Architecture/User - RGB LED Indicator/DIN_5V: D2801.4 (DIN), IC2801.4 (Y), TP2803.1
GND: C401.2, C402.2, C403.2, C404.2, C405.2, C406.2, C407.2, C408.2, C409.2, C410.2, C501.1, C502.1, C503.1, C504.1, C506.2, C507.1, C601.2, C602.2, C603.2, C604.2, C605.2, C616.2, C617.2, C618.2, C701.2, C703.2, C704.2, C801.2, C802.2, C1001.2, C1002.2, C1003.2, C1101.2, C1102.2, C1103.2, C1201.2, C1202.2, C1203.2, C1301.2, C1302.2, C1303.2, C1401.2, C1402.2, C1403.2, C1501.2, C1502.2, C1503.2, C1601.2, C1602.2, C1603.2, C1701.2, C1702.2, C1703.2, C1801.2, C1802.2, C1803.2, C1901.2, C1902.2, C1903.2, C2001.2, C2002.2, C2003.2, C2101.2, C2102.2, C2103.2, C2201.2, C2202.2, C2203.2, C2301.2, C2302.2, C2303.2, C2401.2, C2402.2, C2403.2, C2501.2, C2502.2, C2503.2, C2601.2, C2602.2, C2603.2, C2701.2, C2702.2, C2703.2, C2802.2, C2803.2, C2804.2, C2805.2, C2806.2, C2901.2, C2902.2, C2903.2, C2904.2, D401.2 (GND), D601.2 (A), D2801.3 (VSS), IC1001.7 (GND), IC1001.9 (A1), IC1001.10 (A0), IC1001.17 (PAD), IC1101.7 (GND), IC1101.9 (A1), IC1101.17 (PAD), IC1201.7 (GND), IC1201.9 (A1), IC1201.17 (PAD), IC1301.7 (GND), IC1301.10 (A0), IC1301.17 (PAD), IC1401.7 (GND), IC1401.17 (PAD), IC1501.7 (GND), IC1501.17 (PAD), IC1601.7 (GND), IC1601.10 (A0), IC1601.17 (PAD), IC1701.7 (GND), IC1701.17 (PAD), IC1801.7 (GND), IC1801.17 (PAD), IC1901.7 (GND), IC1901.9 (A1), IC1901.10 (A0), IC1901.17 (PAD), IC2001.7 (GND), IC2001.9 (A1), IC2001.17 (PAD), IC2101.7 (GND), IC2101.9 (A1), IC2101.17 (PAD), IC2201.7 (GND), IC2201.10 (A0), IC2201.17 (PAD), IC2301.7 (GND), IC2301.17 (PAD), IC2401.7 (GND), IC2401.17 (PAD), IC2501.7 (GND), IC2501.10 (A0), IC2501.17 (PAD), IC2601.7 (GND), IC2601.17 (PAD), IC2701.7 (GND), IC2701.17 (PAD), IC2801.1 (~OE), IC2801.3 (GND), IC2802.4 (GND), IC2802.7 (EP), J401.1, J402.5 (GND), J406.1, J501.3, J501.4, J601.A12 (GND), J601.B12 (GND), J601.S1 (SHIELD), Q501.2 (S), Q502.S2, R507.1, R508.2, R509.2, R602.1, R603.1, R607.2, R608.1, R609.1, R701.2, R1001.2, R1101.2, R1201.2, R1301.2, R1401.2, R1501.2, R1601.2, R1701.2, R1801.2, R1901.2, R2001.2, R2101.2, R2201.2, R2301.2, R2401.2, R2501.2, R2601.2, R2701.2, R2801.2, R2901.2, R2902.2, R2903.2, R2904.2, SW402.1, SW402.4, SW403.3, SW403.6, SW404.1, SW404.4, SW405.1, SW405.4, SW406.1, SW406.4, SW407.1, SW407.4, TP1005.1, TP1006.1, TP1106.1, TP1206.1, TP1305.1, TP1605.1, TP1905.1, TP1906.1, TP2006.1, TP2106.1, TP2205.1, TP2505.1, U401.5 (VSS_9), U401.16 (VSSSMPS), U401.31 (VSS_1), U401.57 (VSS_2), U401.58 (ANT_IN), U401.59 (RF_OUT), U401.60 (VSS_3), U401.84 (VSS_4), U401.86 (VSS_5), U501.4 (VSS), U502.6 (V_{SS}), U502.9 (TP), U601.1 (PGND), U601.20 (PGND), U601.21 (TP), U701.3 (GND), U701.5 (TP), U702.2 (GND), U702.5 (Pad), U801.6 (GND), U801.11 (A2), U801.15 (A0), U801.16 (A1), U801.17 (TP), U3202.1 (SDO), U3202.6 (GNDIO), U3202.7 (GND)
unnamed: IC1001.1 (IPROPI), R1001.1
unnamed: IC1101.1 (IPROPI), R1101.1
unnamed: IC1201.1 (IPROPI), R1201.1
unnamed: IC1301.1 (IPROPI), R1301.1
unnamed: IC1401.1 (IPROPI), R1401.1
unnamed: IC1501.1 (IPROPI), R1501.1
unnamed: IC1601.1 (IPROPI), R1601.1
unnamed: IC1701.1 (IPROPI), R1701.1
unnamed: IC1801.1 (IPROPI), R1801.1
unnamed: IC1901.1 (IPROPI), R1901.1
unnamed: IC2001.1 (IPROPI), R2001.1
unnamed: IC2101.1 (IPROPI), R2101.1
unnamed: IC2201.1 (IPROPI), R2201.1
unnamed: IC2301.1 (IPROPI), R2301.1
unnamed: IC2401.1 (IPROPI), R2401.1
unnamed: IC2501.1 (IPROPI), R2501.1
unnamed: IC2601.1 (IPROPI), R2601.1
unnamed: IC2701.1 (IPROPI), R2701.1
unnamed: LED502.1 (K), R510.1
unnamed: Q501.3 (D), R503.2
unnamed: R605.2, R606.1

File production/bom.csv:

Designator,Footprint,Quantity,Value,LCSC Part #
"C1001, C1002, C1203, C1303, C1403, C1503, C1603, C1703, C1803, C1903, C2003, C2103, C2203, C2303, C2403, C2503, C2603, C2703, C2803, C2903, C401, C402, C407, C408, C409, C410, C504, C505, C601, C604, C605, C616, C701, C802, C903",0402,35,100n X7R 16V,
"C1201, C1301, C1401, C1501, C1601, C1701, C1801, C1901, C2001, C2101, C2201, C2301, C2401, C2501, C2601, C2701, C2801, C2901, C602, C617, C618, C702, C703",0603,23,10u X5R 16V,
"C1202, C1302, C1402, C1502, C1602, C1702, C1802, C1902, C2002, C2102, C2202, C2302, C2402, C2502, C2602, C2702, C2802, C2902",0603,18,100n X7R 50V,
"C3001, C3002, C3003, C3004",0603,4,1n X7R 1kV,
"C403, C503, C506",0603,3,4u7 X7R 16V,
"C501, C502",1206,2,47u X5R 16V,
"C603, C801",0603,2,1u X7R 16V,
"C606, C609, C615",0402,3,10n C0G 25V,
"C607, C613",0402,2,470n X5R 25V,
"C608, C614",0402,2,22n X7R 25V,
C610,0402,1,150n X7R 25V,
C611,0402,1,2n2 X7R 25V,
C612,0402,1,390pF X7R 25V,
C901,0603,1,220n X7R 16V,
"C902, C904",0603,2,2u2 X7R 16V,
D401,SOT-23-5,1,ESDS314,
D601,D_SOD-123FL,1,TVS SMF5.0A,
D701,Nexperia_CFP3_SOD-123W,1,Schottky 1N5819W,
D901,INPI22TAT5R5G5B,1,IN-PI22TAT5R5G5B,
"IC1201, IC1301, IC1401, IC1501, IC1601, IC1701, IC1801, IC1901, IC2001, IC2101, IC2201, IC2301, IC2401, IC2501, IC2601, IC2701, IC2801, IC2901",WQFN-16-1EP_3x3mm_P0.5mm_EP1.68x1.68mm_ThermalVias,18,DRV8214RTER,
IC901,SOT-553,1,SN74AHCT1G125DRLR,
IC902,WSON-6-1EP_2x2mm_P0.65mm_EP1x1.6mm,1,REG71050DRVT,
J502,CONN_S2B-PH-SM4-TB_JST,1,S2B-PH-SM4-TB,
J602,USB4125-GF-A,1,USB_C_Receptacle_PowerOnly_6P,
"LED1201, LED1301, LED1401, LED1501, LED1601, LED1701, LED1801, LED1901, LED2001, LED2101, LED2201, LED2301, LED2401, LED2501, LED2601, LED2701, LED2801, LED2901",LED_0603_KingBright,18,BLUE,
"LED501, LED601",LED_0603_KingBright,2,GREEN,
Q501,SOT-23,1,NMOS IRLML6344TRPBF SOT-23,
Q502,CSD85302L,1,CSD85302L,
Q601,Texas_DSBGA-9_1.62x1.58mm_Layout3x3_P0.5mm,1,CSD75207W15,
Q701,SOT-23-3,1,PMOS SI2365EDS-T1-GE3,
"R1001, R1002, R502, R802, R803, R804, R805, R806, R807",0402,9,3k 1%,
"R1201, R1301, R1401, R1501, R1601, R1701, R1801, R1901, R2001, R2101, R2201, R2301, R2401, R2501, R2601, R2701, R2801, R2901",0402,18,680R 1%,
"R1202, R1302, R1402, R1502, R1602, R1702, R1802, R1902, R2002, R2102, R2202, R2302, R2402, R2502, R2602, R2702, R2802, R2902, R401, R501, R505, R601",0402,22,330R 1%,
"R1203, R1303, R1403, R1503, R1603, R1703, R1803, R1903, R2003, R2103, R2203, R2303, R2403, R2503, R2603, R2703, R2803, R2903, R509, R701, R801, R901",0402,22,100k 1%,
"R3001, R3002, R3003, R3004",0603,4,0R 1%,
"R402, R503, R605, R606, R608",0402,5,10k 1%,
"R403, R404",0402,2,22R 1%,
"R504, R508",0402,2,2k2 1%,
"R506, R507",0402,2,4M99 1%,
"R602, R603",0402,2,5k1 1%,
"R604, R607",0402,2,196R 1%,
"SW401, SW402, SW404, SW405, SW406, SW407",SW_KMR232NGULCLFS,6,KMR232NG ULC,
SW403,CAS-D2xx,1,CAS-D20A1,
U1001,Bosch_LGA-14_3x2.5mm_P0.5mm,1,BMI270,
U401,ST-SiP-LGA-86-11x7.3mm,1,STM32WB5MMGH6TR,
U501,WSON-6_1.5x1.5mm_P0.5mm,1,BQ29737DSER,
U502,DFN_2x3mm,1,MCP73831T-2ACI/MC,
U601,Texas_VQFN-RHL-20,1,BQ51013CQWRHLRQ1,
U701,Texas_X2SON-4_1x1mm_P0.65mm,1,TPS3839G33DQNR,
U702,SOT-23-5,1,TPS7A0233DBVR,
U801,Texas_RSA_VQFN-16-1EP_4x4mm_P0.65mm_EP2.16x2.16mm,1,PCA9546ARGVR,

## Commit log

2025-02-28 Added/updated submodules
2025-02-28 Project code main.cpp updated
2025-03-01 Backup almost all code is functionnal
2025-03-10 Updated driver library
2025-03-10 Fixed position control, starting on gpio multiplexing
2025-03-10 Added git mpc23017 submodule
2025-03-13 Control in position working from serial, only tunning left to do
2025-03-28 Finished 65% of schematics
2025-03-31 Added footprints, images, almost finished all èages except for the MCU
2025-04-01 Added RGB LED, added motor connectors, added test points, imported all 3D models
2025-04-04 Finished schematic, imported all footprints, all 3D models and created STM32 project, now need to proofread shematic before layout
2025-04-05 Reviewed shematic, cleaned all DRC errors, chosed stackup, started layout
2025-04-05 Cleaned repo, cleaned and exported shematic, advanced rough layout
2025-04-13 Advanced rough layout
2025-04-14 Finished layout, only cleaning left
2025-04-14 Finished cleaning routing, removed errors, cleaned shematics, added pictures and other improvements
2025-04-17 Added PCB frame
2025-04-19 Added PCB frame for assembly, almost finished auto-review, only MCU and motors left
2025-04-21 Checked everything, corrected footprints, cleaned routing, should be ready to order
2025-04-21 Checked MCU pinout, cleaned shematic, advanced the ioc file
2025-04-24 Final version, cleaned and ordered as is
2025-04-24 Updated ibom
2025-04-24 Added README
2025-05-17 Started on the STM32 firmware
2025-05-19 Working IMU, motors and all, next step, low power..
2025-05-19 Trying to implement the IMU deep sleep / wake-up
2025-05-26 Cleaned repo, remnamed folder, added latest version of drv8214 library
2025-05-27 Updated README and Schematic
2025-06-19 Push before migrating main to functions.h
2025-06-20 Working stop2, starting on BLE
2025-06-23 Abandonned bluetooth, implemented UART comm with DMA
2025-06-25 Fixed the stall behavior and more
2025-09-16 - Readme
